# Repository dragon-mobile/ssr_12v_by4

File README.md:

# Solid State Relays - 12Volts by 4

<br/>

<br/>

The SSR 12Volts by 4 board is one of the open hardware solid state relay
PCB of my Dragon Mobile GitHub organization with a goal to make useful
hardware with associated firmware and software for the tiny home, van life
and maker communities.

## Contributing

Contributors are welcome.
Please note that this project has a [Contributor Covenant Code of Conduct].
By participating in this project you agree to abide by its terms.

All intentionally contributed hardware will be considered to be contributed
under the [CERN] license without any additional terms or conditions.

All intentionally contributed code will be considered to be contributed
under a [MIT] license without any additional terms or conditions.
Please include your information in a comment on all code files for the copyright
etc.

All intentionally contributed documentation, CAD files and libraries, footprints,
artwork or non-code text like this README etc. will be considered to be
contributed under the same [CC-BY-SA] license without any additional terms or
conditions.

Pull requests are always welcome. For major changes, please open an issue first
to discuss what you would like to change.
Please make sure to update or add tests as appropriate for all software changes.

## Licenses

<br/>

All hardware is licensed under the

  * [CERN] - CERN-OHL-W-2.0
  
You can find a copy of the CERN Open Hardware License - Weakly-reciprocal v2.0
in the [LICENSE-CERN-OHL-W-2] file and the how-to guide in the
[CERN-HOWTO_GUIDE] file.

All code is licensed under the

  * [MIT] - MIT License

You can find a copy of the license in the [LICENSE-MIT] file.

All documentation like this README is licensed under the Creative Commons
Attribution-ShareAlike 4.0 International License (CC-BY-SA).

All original CAD files and libraries, footprints, and artwork are also licensed
under the
Creative Commons Attribution-ShareAlike 4.0 International License (CC-BY-SA).
You can find a copy of the [CC-BY-SA] license in the [LICENSE-CC-BY-SA] file.

If after reading the above license files, how-tos, and related FAQs on the
linked license sites on how they apply to the project please either open an
issue or contact me (Michael Cummings) via my Github email and I will try
to guided you through my understanding of how it works.

[CC-BY-SA]: http://creativecommons.org/licenses/by-sa/4.0/
[CERN]: https://ohwr.org/project/cernohl/wikis/Documents/CERN-OHL-version-2
[CERN-HOWTO_GUIDE]: docs/cern_ohl_w_v2_howto.pdf
[Contributor Covenant Code of Conduct]: CODE_OF_CONDUCT.md 
[LICENSE-CC-BY-SA]: LICENSE-CC-BY-SA
[LICENSE-CERN-OHL-W-2]: CERN-OHL-W-2
[LICENSE-MIT]: LICENSE-MIT
[MIT]: https://opensource.org/licenses/MIT

<hr>
Copyright &copy; 2022, Michael Cummings<br/>

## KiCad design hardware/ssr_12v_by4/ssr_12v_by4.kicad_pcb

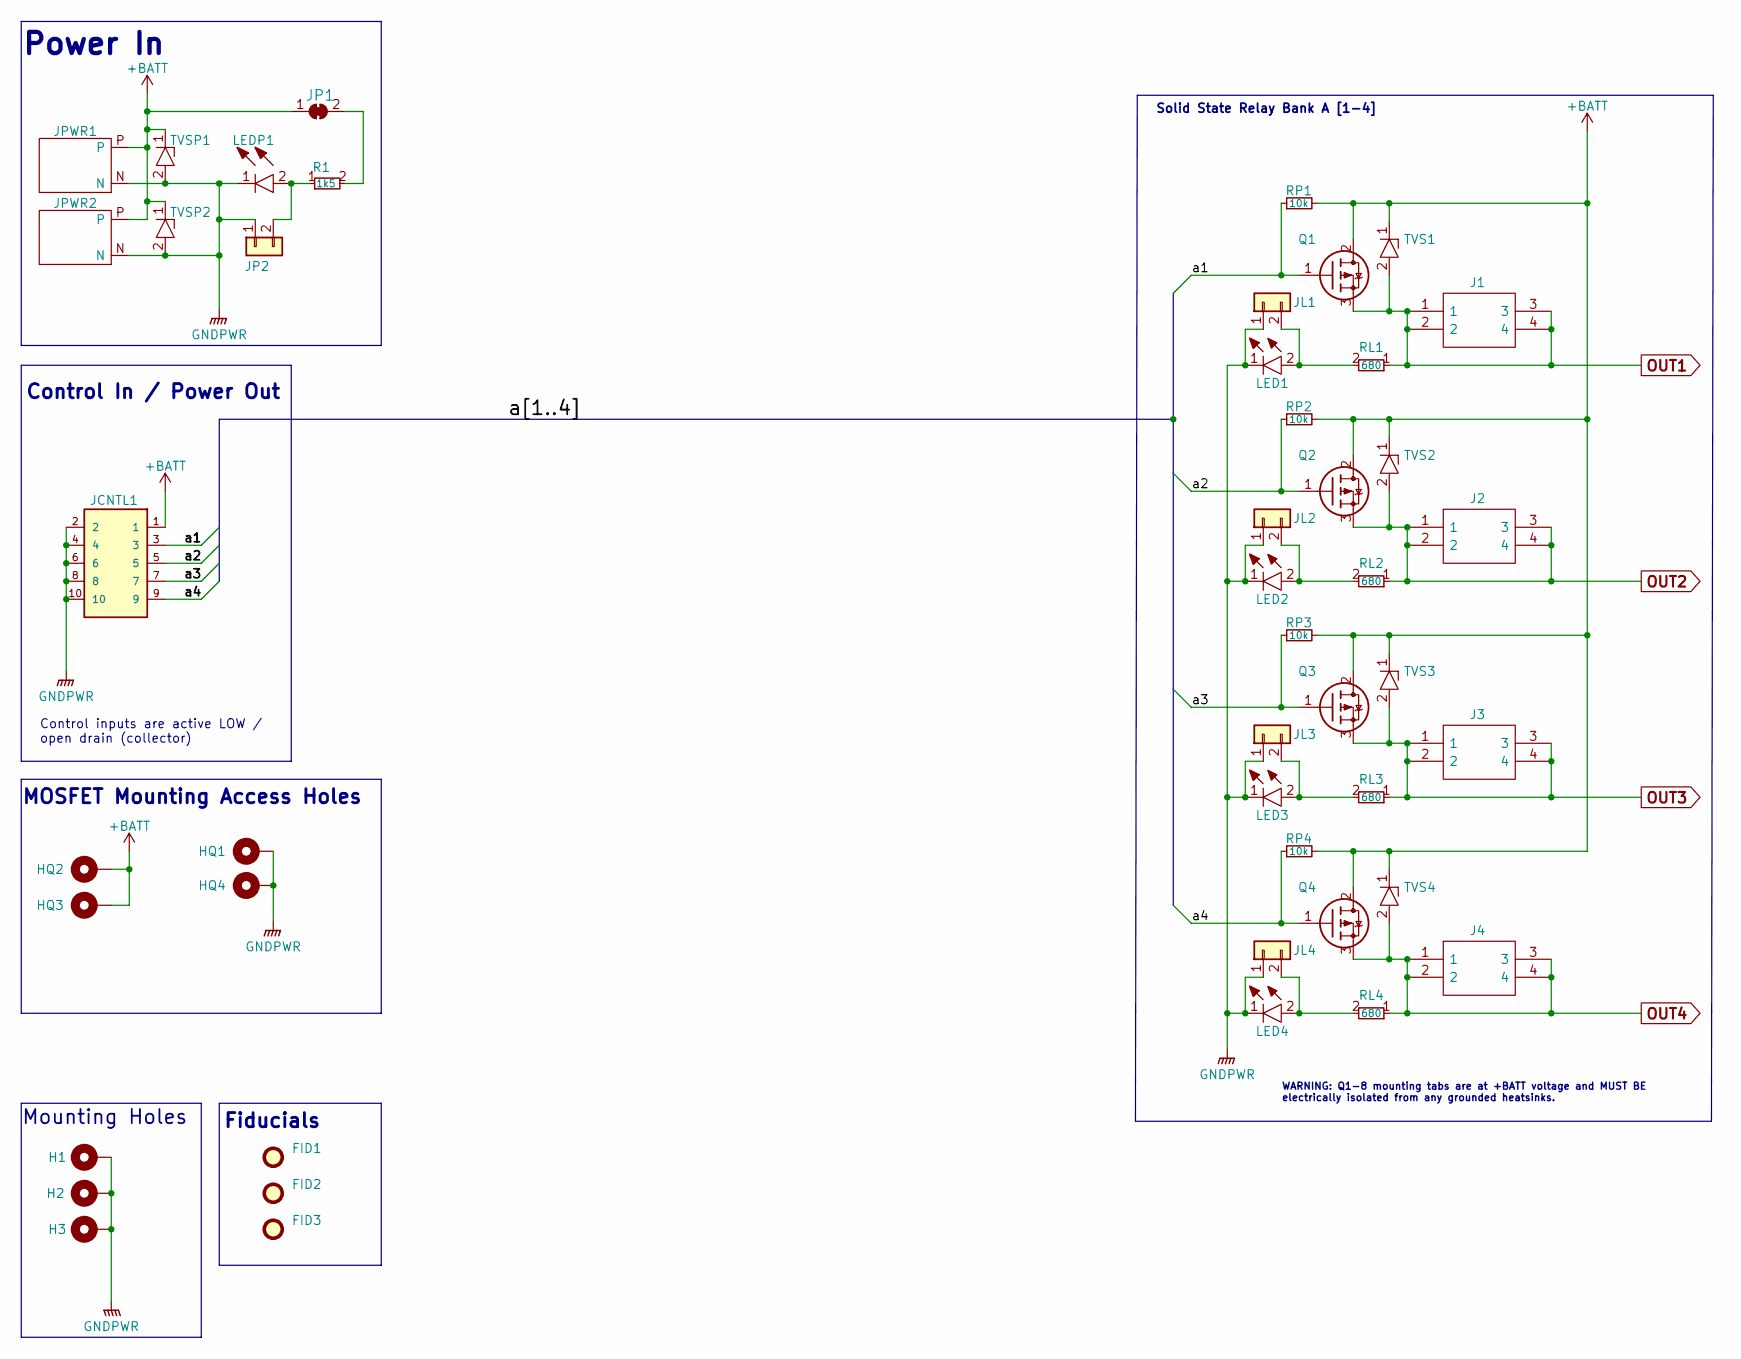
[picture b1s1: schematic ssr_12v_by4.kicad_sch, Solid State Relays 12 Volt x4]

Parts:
FID1, FID2, FID3: Fiducial; Fiducial_0.5mm_Mask1mm
H1, H2, H3: MountingHole; MountingHole_3.2mm_M3_Pad_Via
HQ1, HQ2, HQ3, HQ4: Access Hole; MountingHole_6.1mm_Pad_Via
J1, J2, J3, J4: 1190297; Mouser Part Number 651-1190297
JCNTL1: SHF-105-01-L-D-RA; SAMTEC_SHF-105-01-L-D-RA; PARTREV R
JL1, JL2, JL3, JL4: Conn_01x02; PinHeader_1x02_P1.00mm_Vertical
JP1: SolderJumper_2_Bridged; SolderJumper-2_P1.3mm_Bridged_RoundedPad1.0x1.5mm
JP2: Conn_01x02; PinHeader_1x02_P1.00mm_Vertical
JPWR1, JPWR2: XT60PW-M; XT60PWM
LED1, LED2, LED3, LED4: LTST-C190KFKT; LEDC1607X80N; Mouser Part Number 859-LTST-C190KFKT
LEDP1: LTST-C190KGKT; LEDC1608X80N; Mouser Part Number 859-LTST-C190KGKT
Q1, Q2, Q3, Q4: IRF4905PBF; TO254P469X1042X1967-3P; Mouser Part Number 942-IRF4905PBF
R1: 1k5; RESC2012X65N; Mouser Part Number 755-SDR10EZPJ152
RL1, RL2, RL3, RL4: 680; RESC2012X65N; Mouser Part Number 755-SDR10EZPJ681
RP1, RP2, RP3, RP4: 10k; RESC2012X65N; Mouser Part Number 755-SDR03EZPJ103
TVS1, TVS2, TVS3, TVS4: SM6T16V5AY; SMBJ36CATR; Mouser Part Number 511-SM6T16V5AY
TVSP1, TVSP2: SM6T33AY; SMBJ36CATR; Mouser Part Number 511-SM6T33AY

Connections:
+BATT: HQ2.1, HQ3.1, JCNTL1.1, JP1.1 (A), JPWR1.P, JPWR2.P, Q1.2, Q2.2, Q3.2, Q4.2, RP1.2, RP2.2, RP3.2, RP4.2, TVS1.1, TVS2.1, TVS3.1, TVS4.1, TVSP1.1, TVSP2.1
/a1: JCNTL1.3, Q1.1, RP1.1
/a2: JCNTL1.5, Q2.1, RP2.1
/a3: JCNTL1.7, Q3.1, RP3.1
/a4: JCNTL1.9, Q4.1, RP4.1
GNDPWR: H1.1, H2.1, H3.1, HQ1.1, HQ4.1, JCNTL1.2, JCNTL1.4, JCNTL1.6, JCNTL1.8, JCNTL1.10, JL1.1, JL2.1, JL3.1, JL4.1, JP2.1, JPWR1.N, JPWR2.N, LED1.1, LED2.1, LED3.1, LED4.1, LEDP1.1, TVSP1.2, TVSP2.2
unnamed: JL1.2, LED1.2, RL1.2
unnamed: JL2.2, LED2.2, RL2.2
unnamed: JL3.2, LED3.2, RL3.2
unnamed: JL4.2, LED4.2, RL4.2
unnamed: JP1.2 (B), R1.2
unnamed: JP2.2, LEDP1.2, R1.1
OUT1: J1.1, J1.2, J1.3, J1.4, Q1.3, RL1.1, TVS1.2
OUT2: J2.1, J2.2, J2.3, J2.4, Q2.3, RL2.1, TVS2.2
OUT3: J3.1, J3.2, J3.3, J3.4, Q3.3, RL3.1, TVS3.2
OUT4: J4.1, J4.2, J4.3, J4.4, Q4.3, RL4.1, TVS4.2

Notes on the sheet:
Control inputs are active LOW / open drain (collector)
WARNING: Q1-8 mounting tabs are at +BATT voltage and MUST BE electrically isolated from any grounded heatsinks.
Mounting Holes
Control In / Power Out
MOSFET Mounting Access Holes
Solid State Relay Bank A [1-4]
Power In
Fiducials

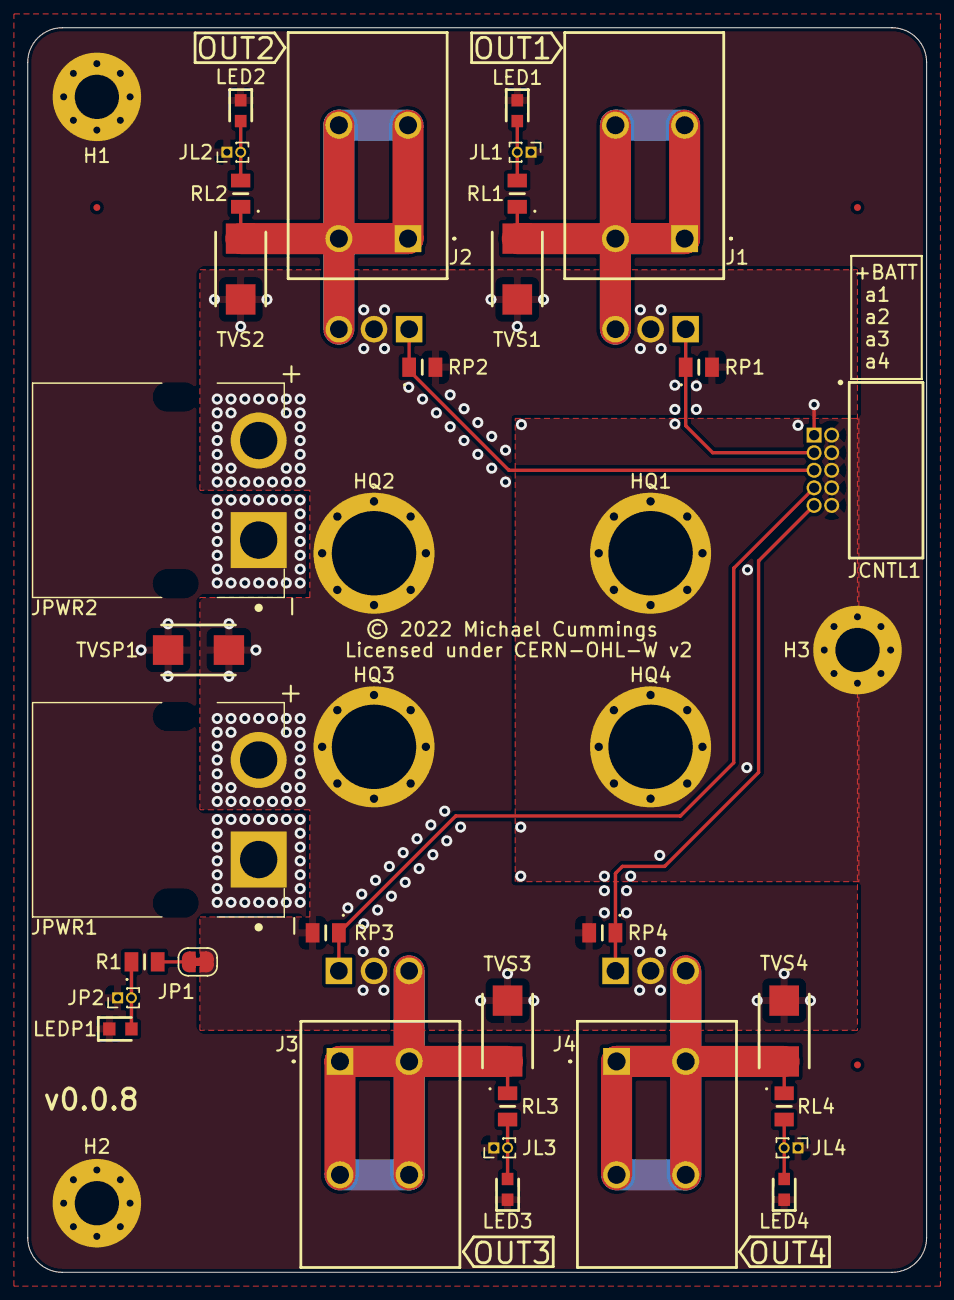
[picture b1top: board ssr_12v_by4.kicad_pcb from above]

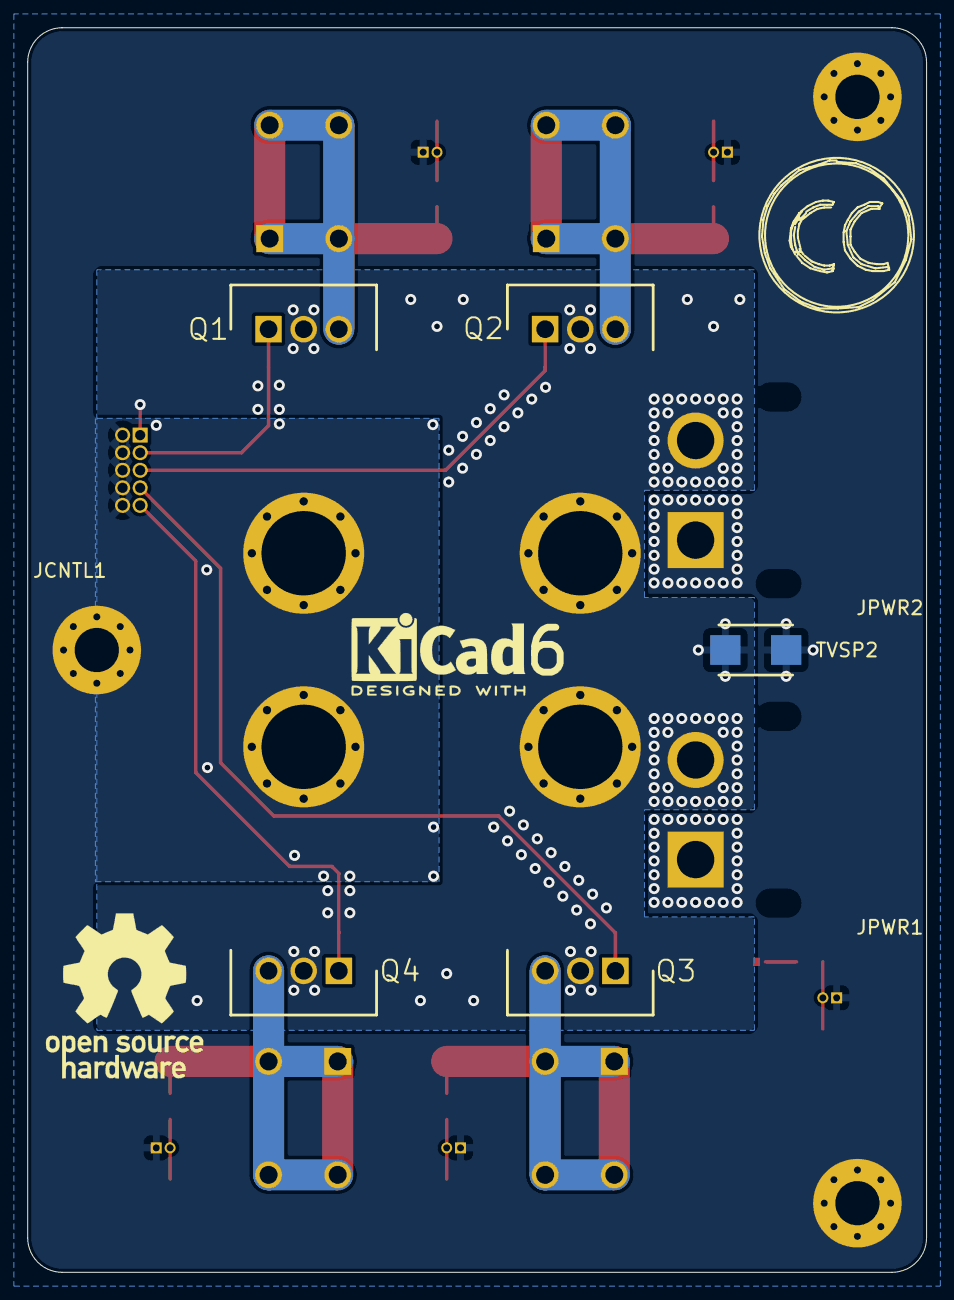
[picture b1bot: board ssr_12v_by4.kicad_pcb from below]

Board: 2 copper layers, 65.0 x 90.0 mm, 47 parts (5 on the bottom side), 16 nets.

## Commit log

2023-01-03 README.md, license files etc.
2023-01-04 Part 1 of 'Never To Much Silkscreen'
2023-01-04 Fixed incorrect URLs in README
2023-01-04 Added needed files in docs/ for README link

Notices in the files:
README.md:
https://img.shields.io/static/v1?label=license&message=CERN-OHL-W-2.0%20%2F%20MIT%20%2F%20CC-BY-SA-4.0&color=orange
CC BY-SA 4.0
hardware/ssr_12v_by4/ssr_12v_by4.kicad_pcb:
creativecommons.org/licenses/by/4.0
License: CC By 4.0
Licensed under CERN-OHL-W v2
